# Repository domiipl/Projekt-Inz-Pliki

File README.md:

# Wstęp i informacje o projekcie
Cześć, jesteśmy grupą studentów, którzy na swój projekt inżynierski postanowili stworzyć niedużego robota sterowanego za pomocą interaktywnej maty.

Robot sterowany jest za pomocą sekwencji, które wprowadzamy na wyżej wymienionej macie. Możemy dawać mu proste komendy pozwalające na poruszanie się. Alternatywnym trybem jest jazda swobodna pozwalająca na sterowanie robotem w czasie rzeczywistym. Mata jest urządzeniem posiadającym układ przycisków 4x4 i ekran pokazujący aktualnie wpisywaną sekwencję. Posiadając podstawową wiedzę na temat programowania i elektroniki, będziesz mógł skonstruować taki zestaw sam, w zaciszu swojego domu. 

Bardziej szczegółowe informacje na temat samego projektu znajdziesz w samym poradniku.

Repozytorium jest podzielone na pięć folderów.
Dzielą się one na:
* **Kod robota** - znajduje się tu gotowy kod, dzięki któremu robot będzie w stanie się poruszać.
* **Kod maty** - znajduje się tu gotowy kod, dzięki któremu będziemy w stanie wysyłać komendy z maty do robota.
* **Schemat robota** - wymagane pliki do zamówienia płytki pcb do robota.
* **Schemat maty** - wymagane pliki do zamówienia płytki pcb do robota.
* **Instruktaż** - szczegółowy poradnik zawierający wymagane materiały oraz opis budowy robota i maty.

Zalecamy z zapoznaniem się dokładnie z poradnikiem przed próbą konstrukcji. Spis treści znajdziesz w pliku README w folderze "Instruktaż".

Powodzenia!

Chcielibyśmy tutaj jeszcze dodać, że wykonując projekt trzeba liczyć się z pewnymi wydatkami.
Orientacyjne koszty na dzień 16 stycznia 2020:
* **Robot** - Koszt wszystkich części robota to około 130zł, jeśli kupujemy na botlandzie. Można zmniejszyć koszta kupując części na przykład na aliexpress, jednak wydłuży to czas w jakim części do nas przyjdą.
* **Mata** - Koszt wszystkich części maty wynosi około 205zł, podobna sytuacja jak z częściami u robota, koszty można zmniejszyć kupując na przykład z allegro lub aliexpress.

Zdjęcia końcowe produktów:

**Robot**

**Mata**

Filmy przedstawiające działanie projektu:

[Tryb komend](https://www.youtube.com/watch?v=S5_3_hodGV8)

[Tryb swobodny](https://www.youtube.com/watch?v=uaEHo7fgwFo)

W razie problemów, możesz kontaktować się z nami pod tym adresem e-mail:
## **projektinzrobot@gmail.com**

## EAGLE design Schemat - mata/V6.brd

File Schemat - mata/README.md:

# Pliki potrzebne podczas zamawiania płytek PCB przez internet.
**Najważniejszym jest plik spakowany, ponieważ zawiera kilka istotnych plików do zamówienia internetowego.**

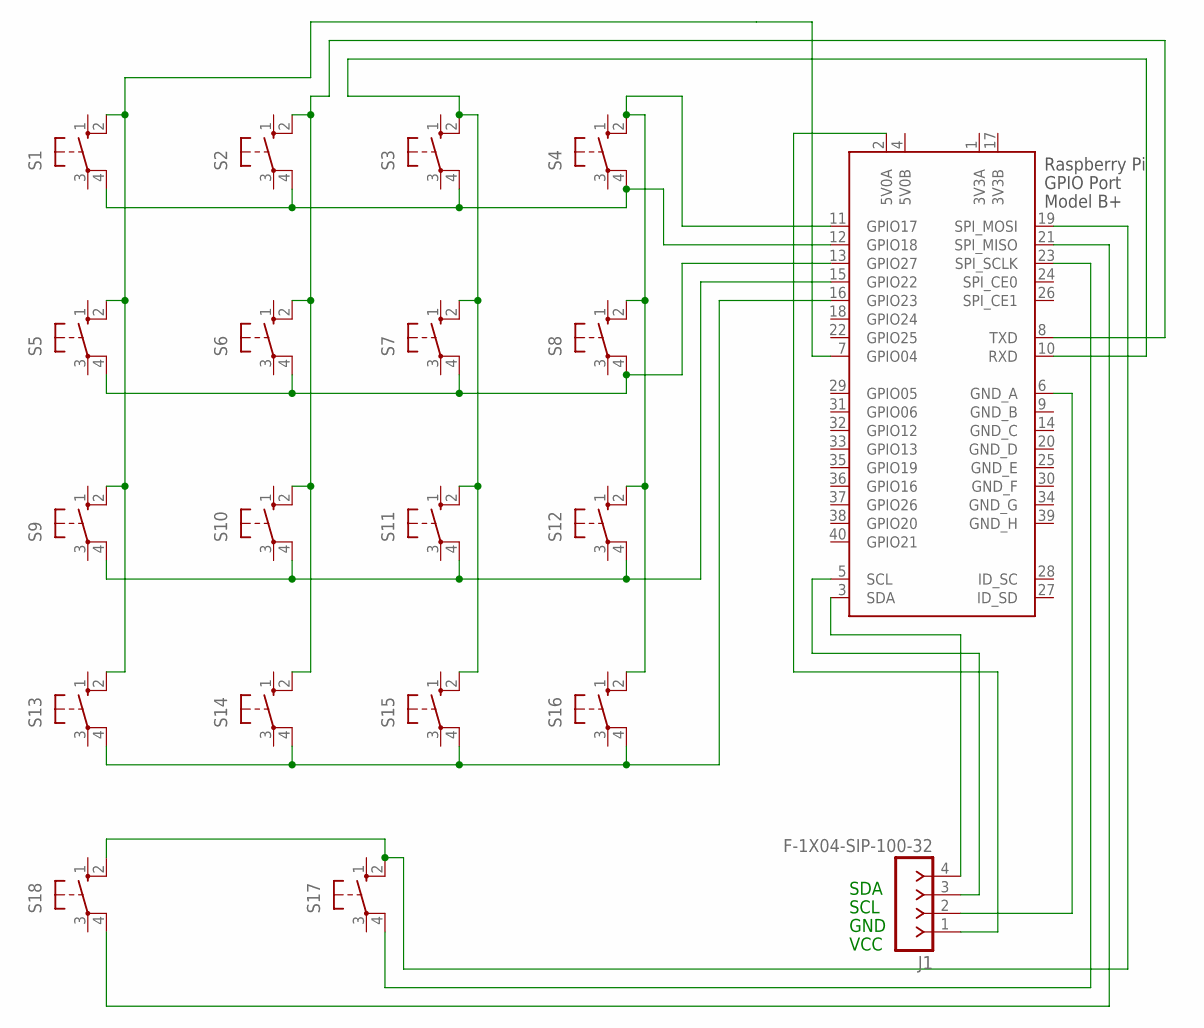
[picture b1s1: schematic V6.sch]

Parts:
J1: F-1X04-SIP-100-32; SIP-100-04-32
S1, S2, S3, S4, S5, S6, S7, S8, S9, S10, S11, S12, S13, S14, S15, S16, S17, S18: 40-XX; B3F-40XX
X1: RASPI_GPIO_B+#_PIN; RASPI_GPIO_B+_PIN

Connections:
3V3A: X1.1 (3V3A)
3V3B: X1.17 (3V3B)
5V0B: X1.4 (5V0B)
GND_B: X1.9 (GND_B)
GND_C: X1.14 (GND_C)
GND_D: X1.20 (GND_D)
GND_E: X1.25 (GND_E)
GND_F: X1.30 (GND_F)
GND_G: X1.34 (GND_G)
GND_H: X1.39 (GND_H)
unnamed: S1.2 (S1), S5.2 (S1), S9.2 (S1), S13.2 (S1), X1.7 (GPIO04)
unnamed: S2.2 (S1), S6.2 (S1), S10.2 (S1), S14.2 (S1), X1.8 (TXD)
unnamed: J1.1, X1.2 (5V0A)
unnamed: J1.4, X1.3 (SDA)
unnamed: S13.4 (P1), S14.4 (P1), S15.4 (P1), S16.4 (P1), X1.16 (GPIO23)
unnamed: S9.4 (P1), S10.4 (P1), S11.4 (P1), S12.4 (P1), X1.15 (GPIO22)
unnamed: S5.4 (P1), S6.4 (P1), S7.4 (P1), S8.4 (P1), X1.13 (GPIO27)
unnamed: S1.4 (P1), S2.4 (P1), S3.4 (P1), S4.4 (P1), X1.12 (GPIO18)
unnamed: S3.2 (S1), S7.2 (S1), S11.2 (S1), S15.2 (S1), X1.10 (RXD)
unnamed: S18.4 (P1), X1.21 (SPI_MISO)
unnamed: S17.4 (P1), X1.23 (SPI_SCLK)
unnamed: J1.3, X1.5 (SCL)
unnamed: J1.2, X1.6 (GND_A)
unnamed: S17.2 (S1), S18.2 (S1), X1.19 (SPI_MOSI)
unnamed: S4.2 (S1), S8.2 (S1), S12.2 (S1), S16.2 (S1), X1.11 (GPIO17)

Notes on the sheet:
SDA
SCL
GND
VCC

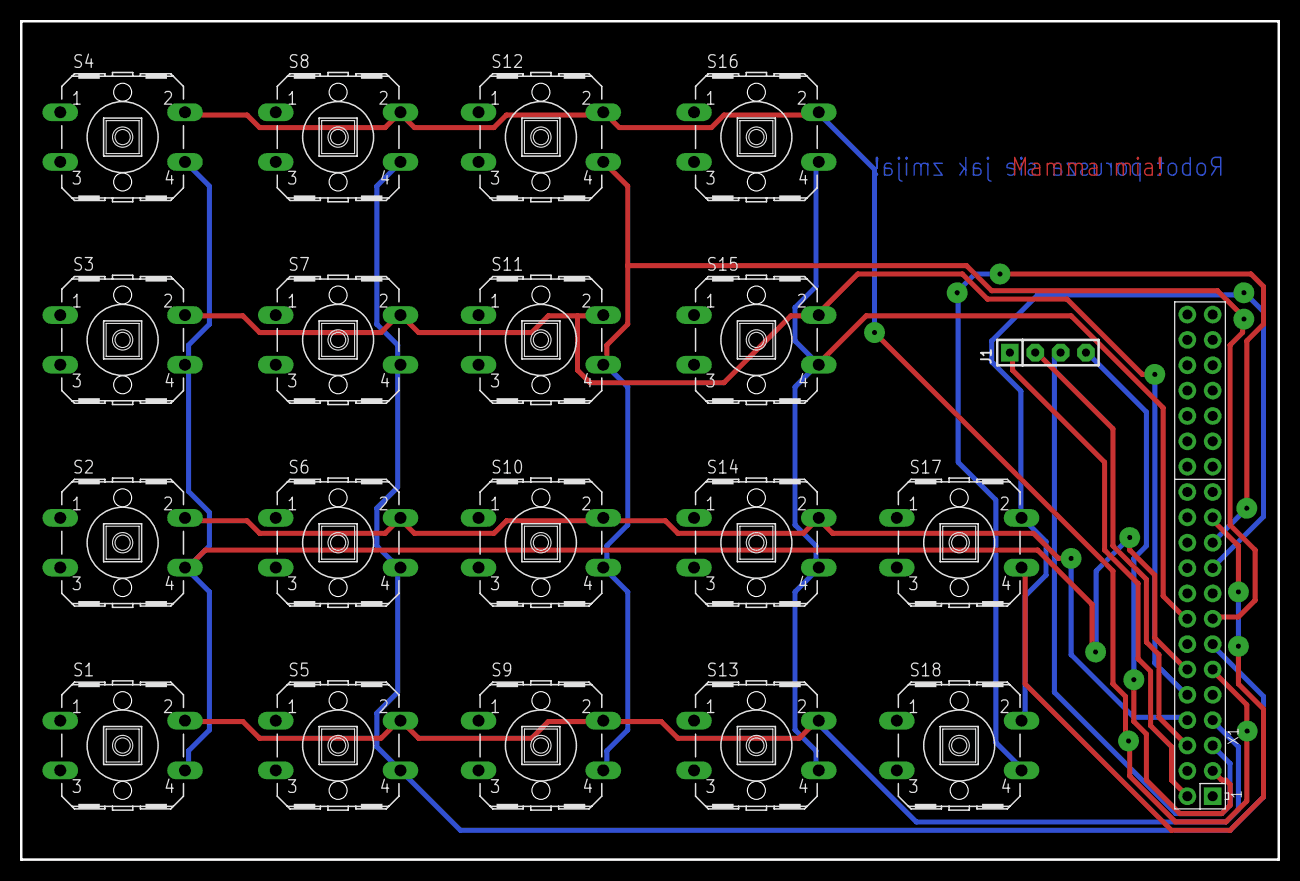
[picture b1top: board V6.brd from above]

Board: 2 copper layers, 126.0 x 84.0 mm, 20 parts (0 on the bottom side), 15 nets.

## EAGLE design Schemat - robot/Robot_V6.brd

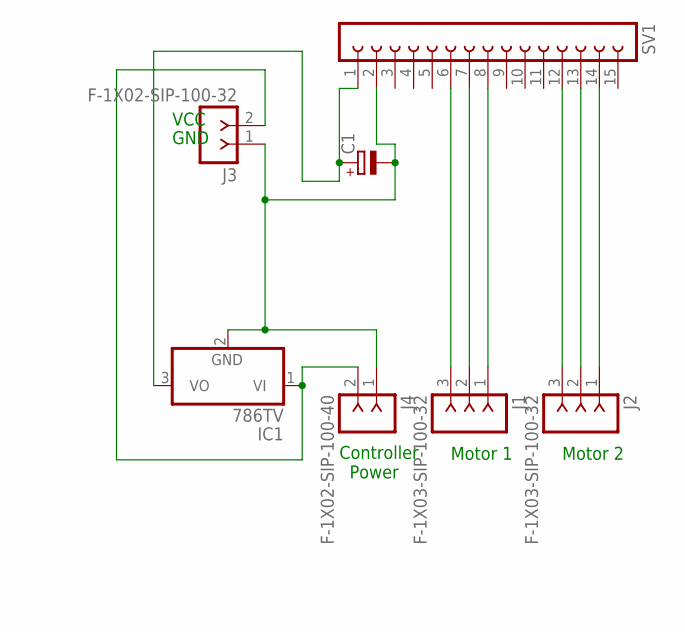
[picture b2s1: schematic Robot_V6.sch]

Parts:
C1: CPOL-EUE1.8-4; E1,8-4
IC1: 786TV; TO220V
J1, J2: F-1X03-SIP-100-32; SIP-100-03-32
J3: F-1X02-SIP-100-32; SIP-100-02-32
J4: F-1X02-SIP-100-40; SIP-100-02-40
SV1: FE15-1; FE15

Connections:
unnamed: C1.-, IC1.2 (GND), J3.1, J4.1, SV1.2
unnamed: J2.1, SV1.14
unnamed: J2.2, SV1.13
unnamed: J2.3, SV1.12
unnamed: J1.1, SV1.8
unnamed: J1.2, SV1.7
unnamed: J1.3, SV1.6
unnamed: IC1.1 (VI), J3.2, J4.2
unnamed: C1.+, IC1.3 (VO), SV1.1

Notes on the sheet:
Motor 1
Motor 2
VCC
GND
Controller Power

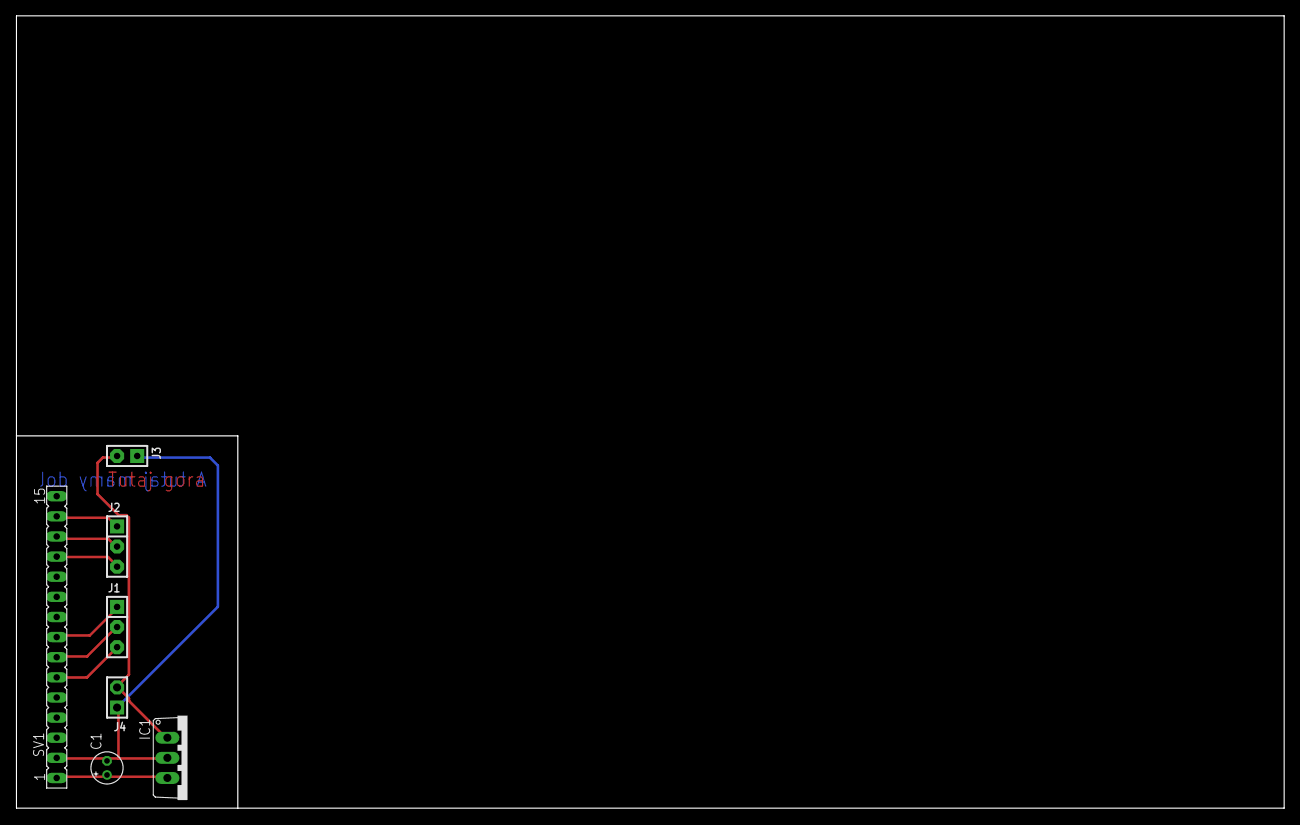
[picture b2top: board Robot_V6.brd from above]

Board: 2 copper layers, 160.0 x 100.0 mm, 7 parts (0 on the bottom side), 9 nets.

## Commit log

2020-01-07 potrzebne materiały
2020-01-12 poprawki
2020-01-12 aktualizacja poradnika i dodanie kodu maty do plikow
2020-01-13 dodanie pliku
2020-01-14 zmiany w poradniku
2020-01-15 plik z bibliotekami do raspa
2020-01-15 poprawki kod mata
2020-01-15 plik do ustawienia maliny jako serwis
2020-01-15 mała poprawka
2020-01-15 mata - zly pin
2020-01-15 mata - hotfix
2020-01-15 mata - zmiana start z tryb
2020-01-15 zmiany
2020-01-15 małe poprawki
2020-01-15 mini poprawka
2020-01-15 próba md
2020-01-15 test
2020-01-15 test2
2020-01-15 dodanie kolejnych zdjęć
2020-01-15 ciąg dalszy
2020-01-16 zmiana zdjęcia schematu
2020-01-16 dodanie informacji o projekcie
2020-01-17 aktualizacja schematów
2020-01-19 poprawa nazw zdjęć
2020-01-21 aktualizacja
2020-01-21 aktualizacja zdjęcia
2020-01-23 zdjęcie obudowy
2020-01-23 projekt obudowy

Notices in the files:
parts and their libraries:
con-headers-jp: Copyright (C) 2008, Bob Starr
